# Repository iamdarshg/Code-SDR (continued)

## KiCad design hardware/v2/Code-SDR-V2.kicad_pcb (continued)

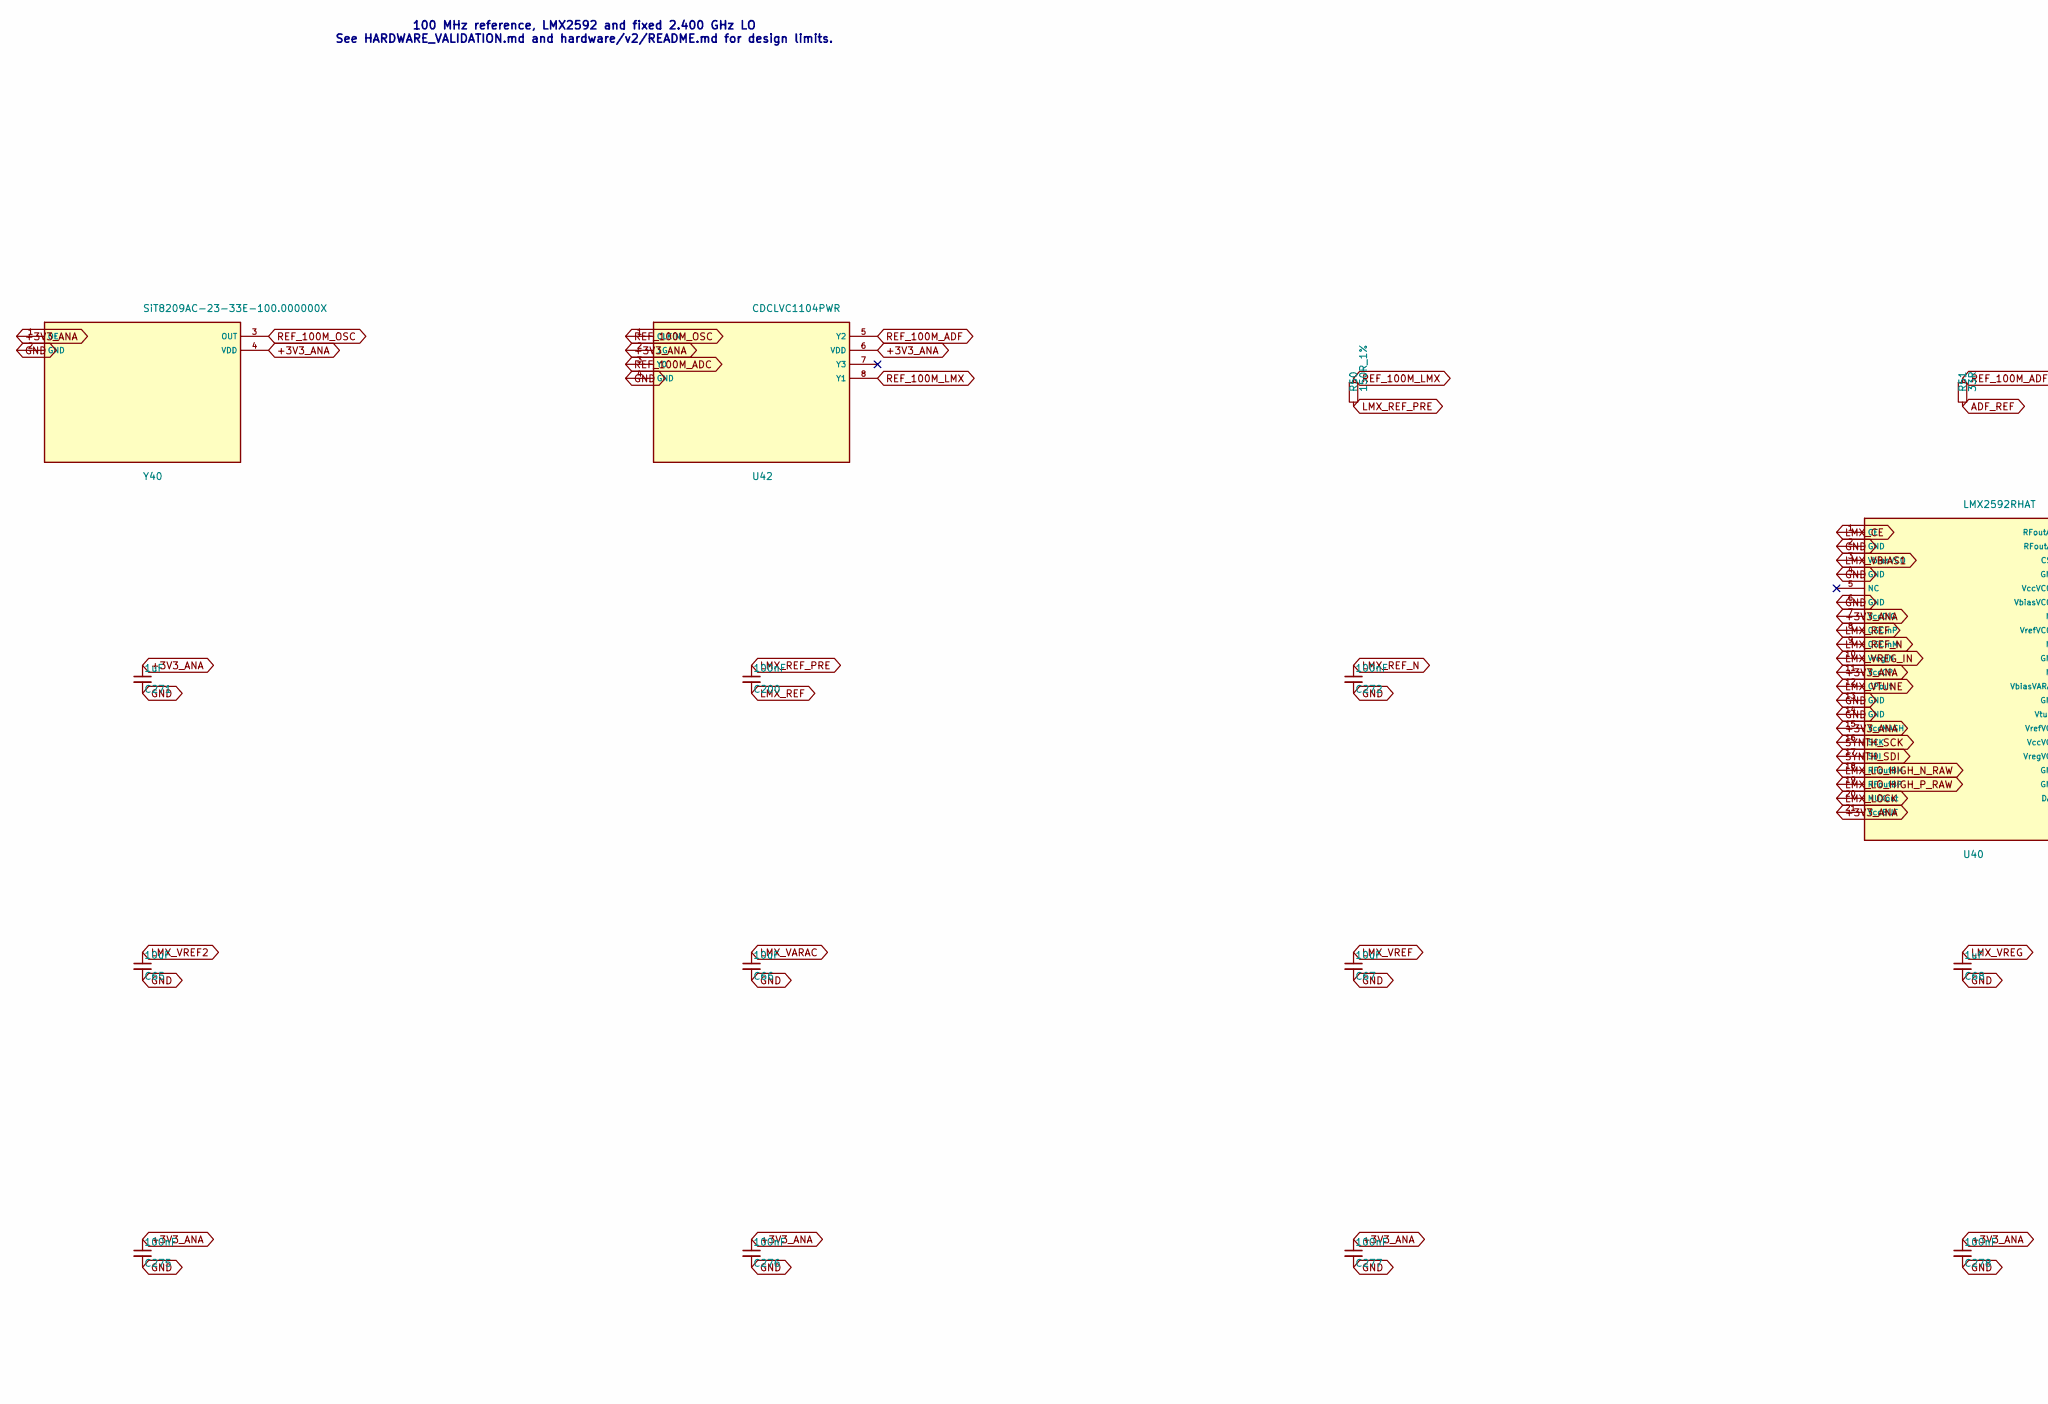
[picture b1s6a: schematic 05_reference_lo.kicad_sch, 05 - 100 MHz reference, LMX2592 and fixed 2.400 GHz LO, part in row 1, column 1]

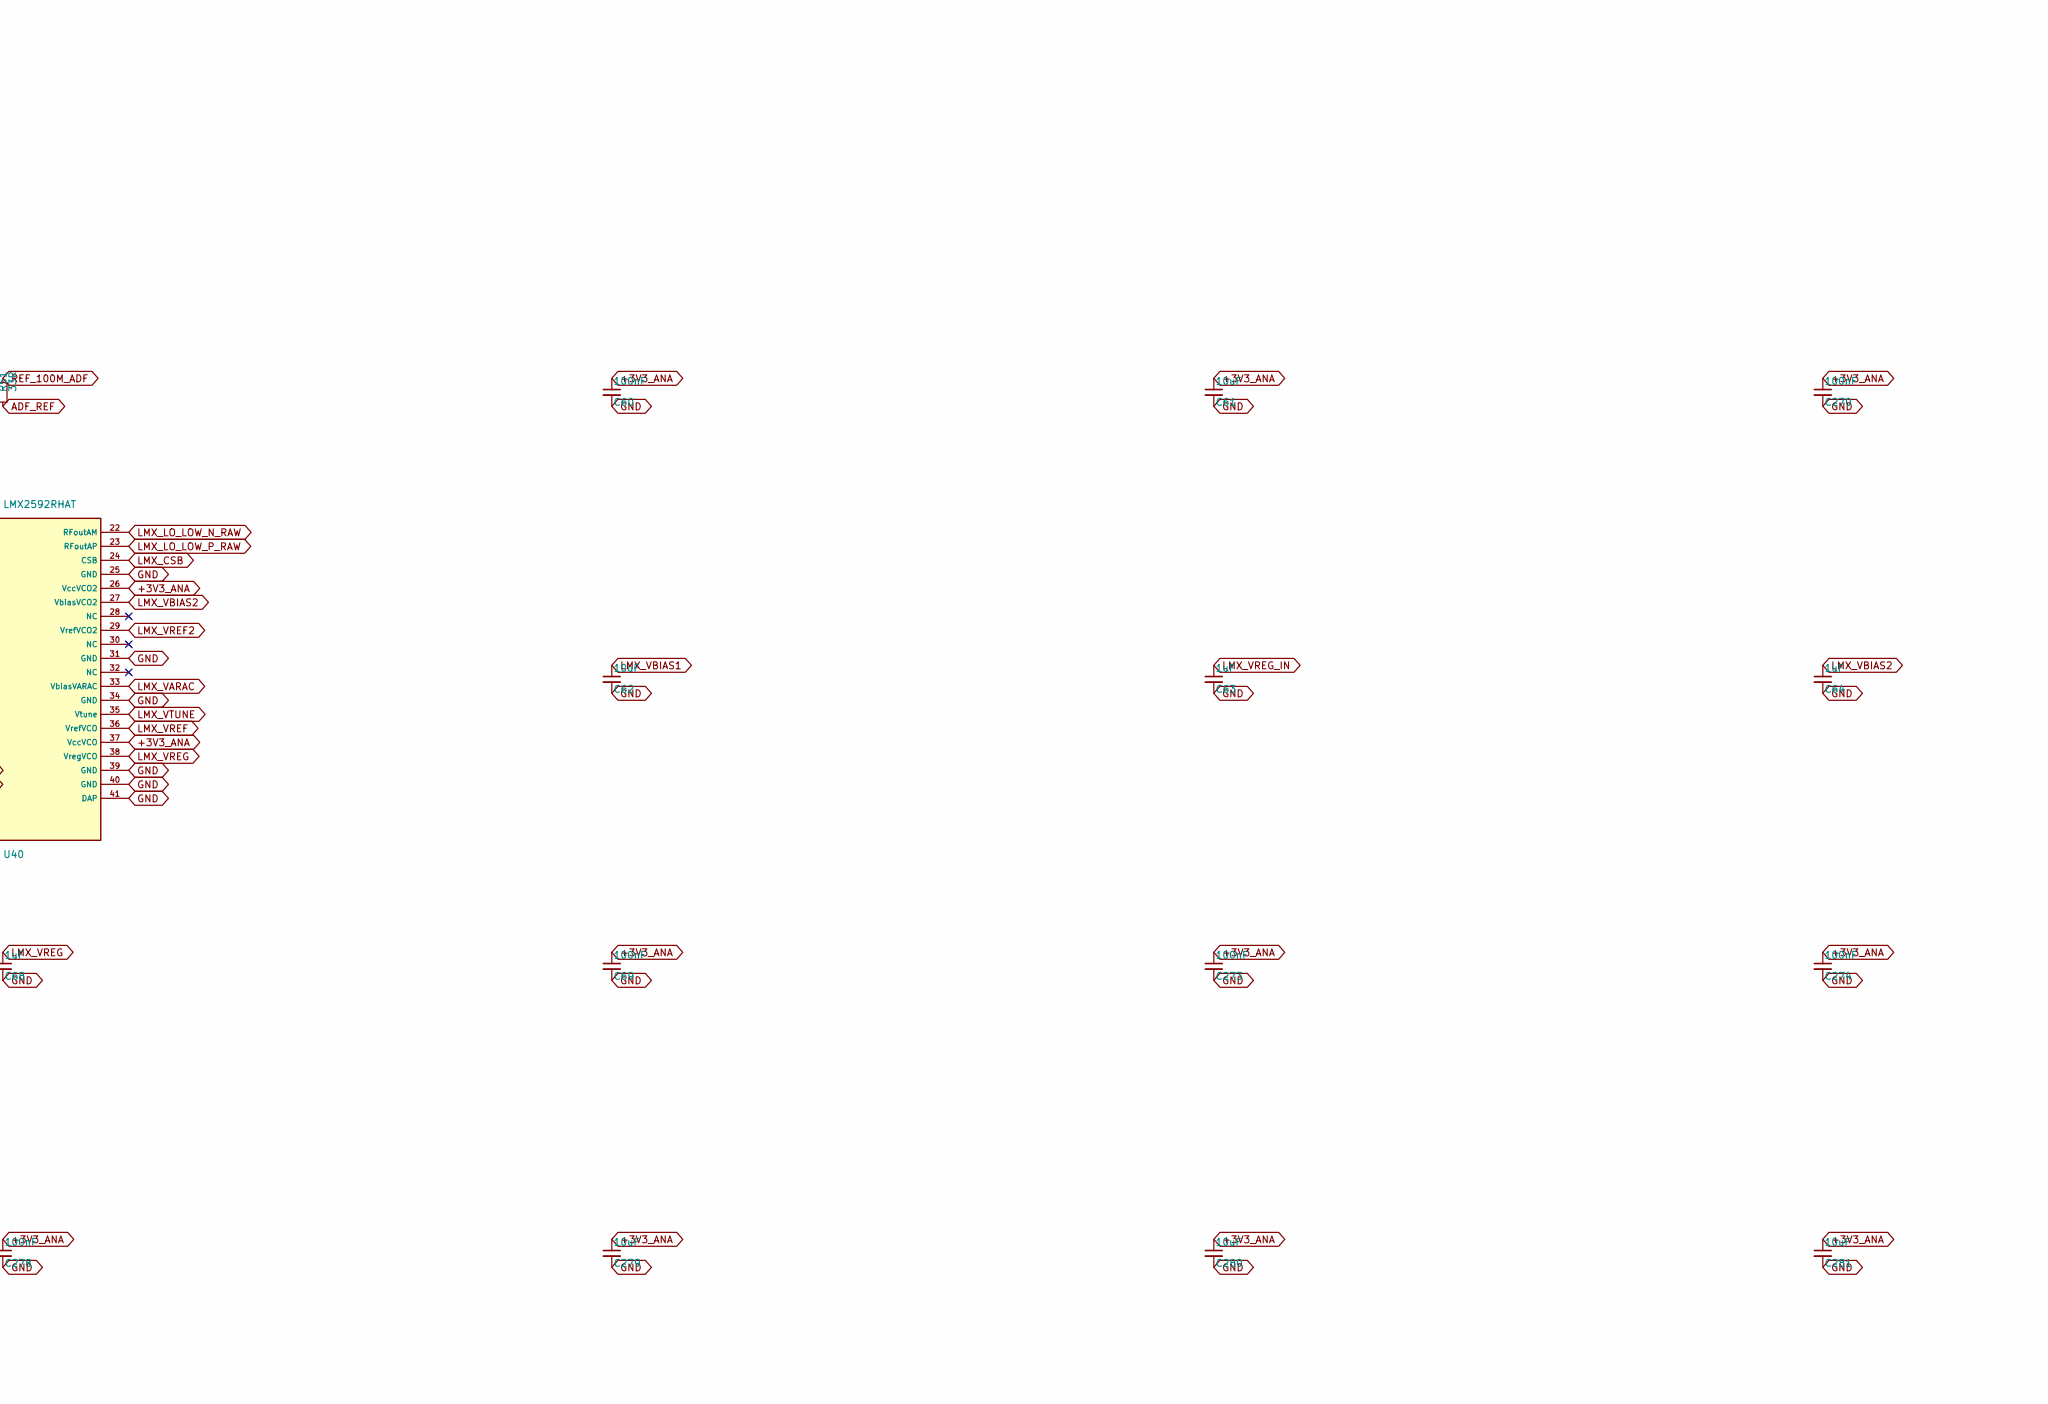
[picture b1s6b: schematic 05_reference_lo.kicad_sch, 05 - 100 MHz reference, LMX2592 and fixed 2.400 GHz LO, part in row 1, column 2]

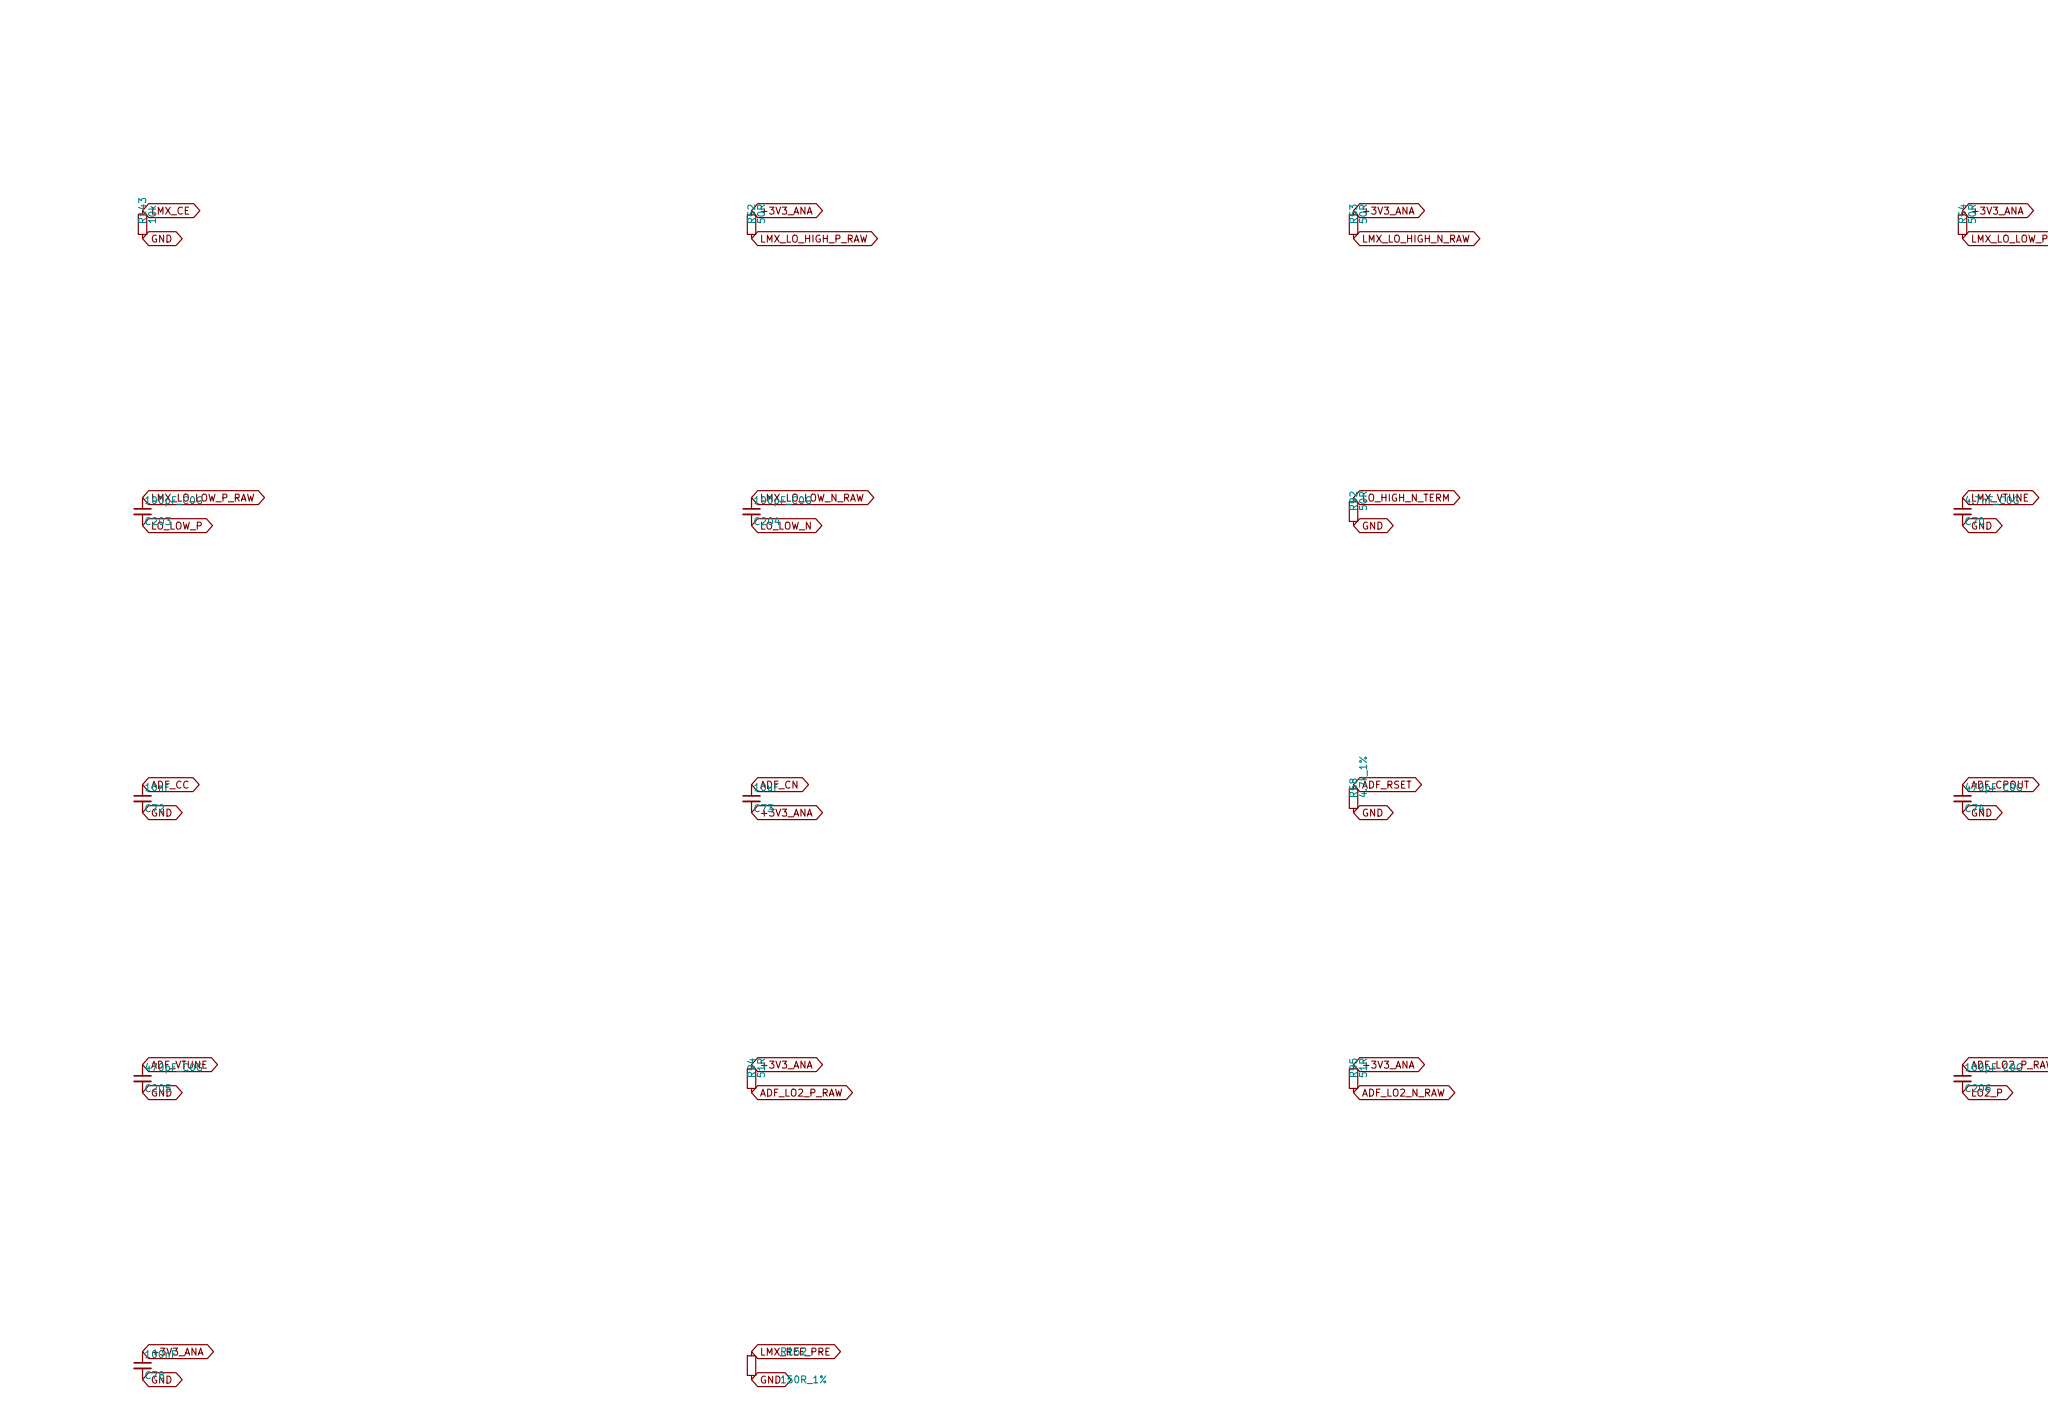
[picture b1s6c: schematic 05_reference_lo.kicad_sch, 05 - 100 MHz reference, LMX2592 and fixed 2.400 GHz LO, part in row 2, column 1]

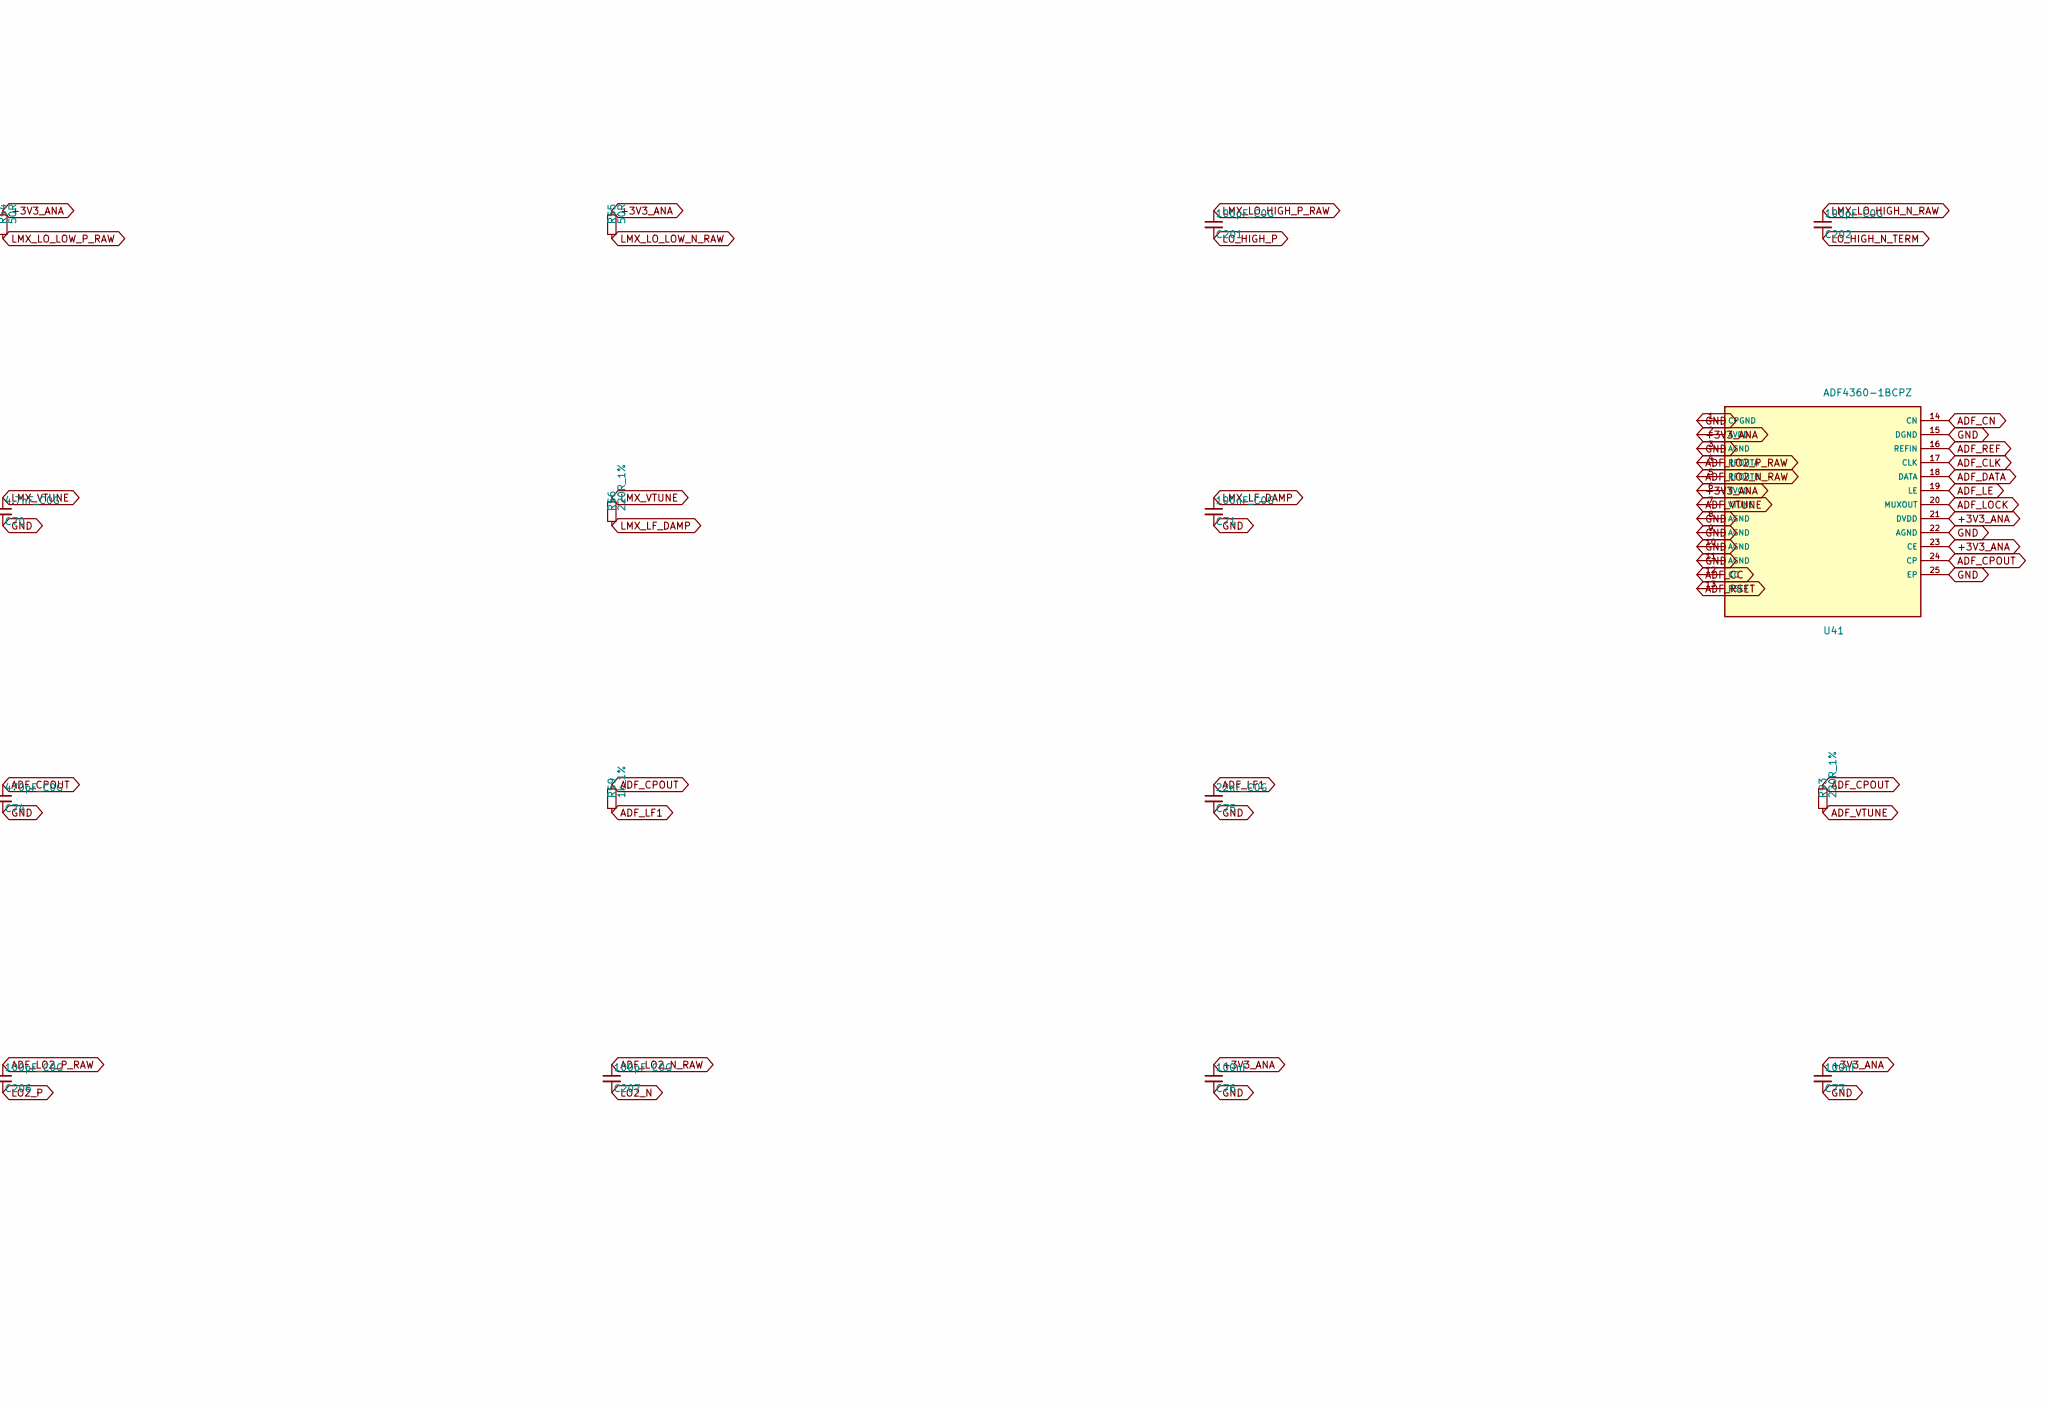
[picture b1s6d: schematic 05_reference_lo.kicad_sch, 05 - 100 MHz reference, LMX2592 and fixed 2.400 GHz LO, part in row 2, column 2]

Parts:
C60, C69, C76, C77, C78, C200, C270, C272, C273, C274, C275, C276, C277, C278: 100nF; C_0402_1005Metric
C61, C62, C65, C66, C67, C73, C279, C280, C281: 10uF; C_0805_2012Metric
C63, C64, C68, C271: 1uF; C_0603_1608Metric
C70: 4.7nF_C0G; C_0402_1005Metric
C71: 100nF_C0G; C_1206_3216Metric
C72: 10nF; C_0402_1005Metric
C74, C205: 470pF_C0G; C_0402_1005Metric
C75: 22nF_C0G; C_0805_2012Metric
C201, C202, C203, C204, C206, C207: 100pF_C0G; C_0201_0603Metric
R50, R152: 150R_1%; R_0402_1005Metric
R51: 33R; R_0402_1005Metric
R52, R53, R54, R55: 50R; R_0402_1005Metric
R56, R93: 220R_1%; R_0402_1005Metric
R58: 4.7k_1%; R_0402_1005Metric
R59: 1k_1%; R_0402_1005Metric
R92: 50R; R_0201_0603Metric
R94, R95: 51R; R_0402_1005Metric
R143: 10k; R_0402_1005Metric
U40: LMX2592RHAT; Texas_RHA0040B_VQFN-40-1EP_6x6mm_P0.5mm_EP4.15x4.15mm_Therm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
U41: ADF4360-1BCPZ; LFCSP-24-1EP_4x4mm_P0.5mm_EP2.5x2.5mm_ThermalVias
U42: CDCLVC1104PWR; TSSOP-8_4.4x3mm_P0.65mm
Y40: SiT8209AC-23-33E-100.000000X; Oscillator_SMD_SiT_PQFN-4Pin_3.2x2.5mm

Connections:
+3V3_ANA: C60.1, C61.1, C69.1, C73.2, C76.1, C77.1, C78.1, C270.1, C271.1, C273.1, C274.1, C275.1, C276.1, C277.1, C278.1, C279.1, C280.1, C281.1, R52.1, R53.1, R54.1, R55.1, R94.1, R95.1, U40.7 (VccDIG), U40.11 (VccCP), U40.15 (VccMASH), U40.21 (VccBUF), U40.26 (VccVCO2), U40.37 (VccVCO), U41.2 (AVDD), U41.6 (VVCO), U41.21 (DVDD), U41.23 (CE), U42.2 (1G), U42.6 (VDD), Y40.1 (OE), Y40.4 (VDD); also elsewhere on the board
ADF_CC: C72.1, U41.12 (CC)
ADF_CLK: U41.17 (CLK); also elsewhere on the board
ADF_CN: C73.1, U41.14 (CN)
ADF_CPOUT: C74.1, R59.1, R93.1, U41.24 (CP)
ADF_DATA: U41.18 (DATA); also elsewhere on the board
ADF_LE: U41.19 (LE); also elsewhere on the board
ADF_LF1: C75.1, R59.2
ADF_LO2_N_RAW: C207.1, R95.2, U41.5 (RFOUTB)
ADF_LO2_P_RAW: C206.1, R94.2, U41.4 (RFOUTA)
ADF_LOCK: U41.20 (MUXOUT); also elsewhere on the board
ADF_REF: R51.2, U41.16 (REFIN)
ADF_RSET: R58.1, U41.13 (RSET)
ADF_VTUNE: C205.1, R93.2, U41.7 (VTUNE)
LMX_CE: R143.1, U40.1 (CE); also elsewhere on the board
LMX_CSB: U40.24 (CSB); also elsewhere on the board
LMX_LF_DAMP: C71.1, R56.2
LMX_LOCK: U40.20 (MUXout); also elsewhere on the board
LMX_LO_HIGH_N_RAW: C202.1, R53.2, U40.18 (RFoutBM)
LMX_LO_HIGH_P_RAW: C201.1, R52.2, U40.19 (RFoutBP)
LMX_LO_LOW_N_RAW: C204.1, R55.2, U40.22 (RFoutAM)
LMX_LO_LOW_P_RAW: C203.1, R54.2, U40.23 (RFoutAP)
LMX_REF: C200.2, U40.8 (OSCinP)
LMX_REF_N: C272.1, U40.9 (OSCinM)
LMX_REF_PRE: C200.1, R50.2, R152.1
LMX_VARAC: C66.1, U40.33 (VbiasVARAC)
LMX_VBIAS1: C62.1, U40.3 (VbiasVCO)
LMX_VBIAS2: C64.1, U40.27 (VbiasVCO2)
LMX_VREF: C67.1, U40.36 (VrefVCO)
LMX_VREF2: C65.1, U40.29 (VrefVCO2)
LMX_VREG: C68.1, U40.38 (VregVCO)
LMX_VREG_IN: C63.1, U40.10 (VregIN)
LMX_VTUNE: C70.1, R56.1, U40.12 (CPout), U40.35 (Vtune)
LO2_N: C207.2; also elsewhere on the board
LO2_P: C206.2; also elsewhere on the board
LO_HIGH_N_TERM: C202.2, R92.1
LO_HIGH_P: C201.2; also elsewhere on the board
LO_LOW_N: C204.2; also elsewhere on the board
LO_LOW_P: C203.2; also elsewhere on the board
REF_100M_ADC: U42.3 (Y0); also elsewhere on the board
REF_100M_ADF: R51.1, U42.5 (Y2)
REF_100M_LMX: R50.1, U42.8 (Y1)
REF_100M_OSC: U42.1 (CLKIN), Y40.3 (OUT)
SYNTH_SCK: U40.16 (SCK); also elsewhere on the board
SYNTH_SDI: U40.17 (SDI); also elsewhere on the board

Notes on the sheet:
100 MHz reference, LMX2592 and fixed 2.400 GHz LO See HARDWARE_VALIDATION.md and hardware/v2/README.md for design limits.

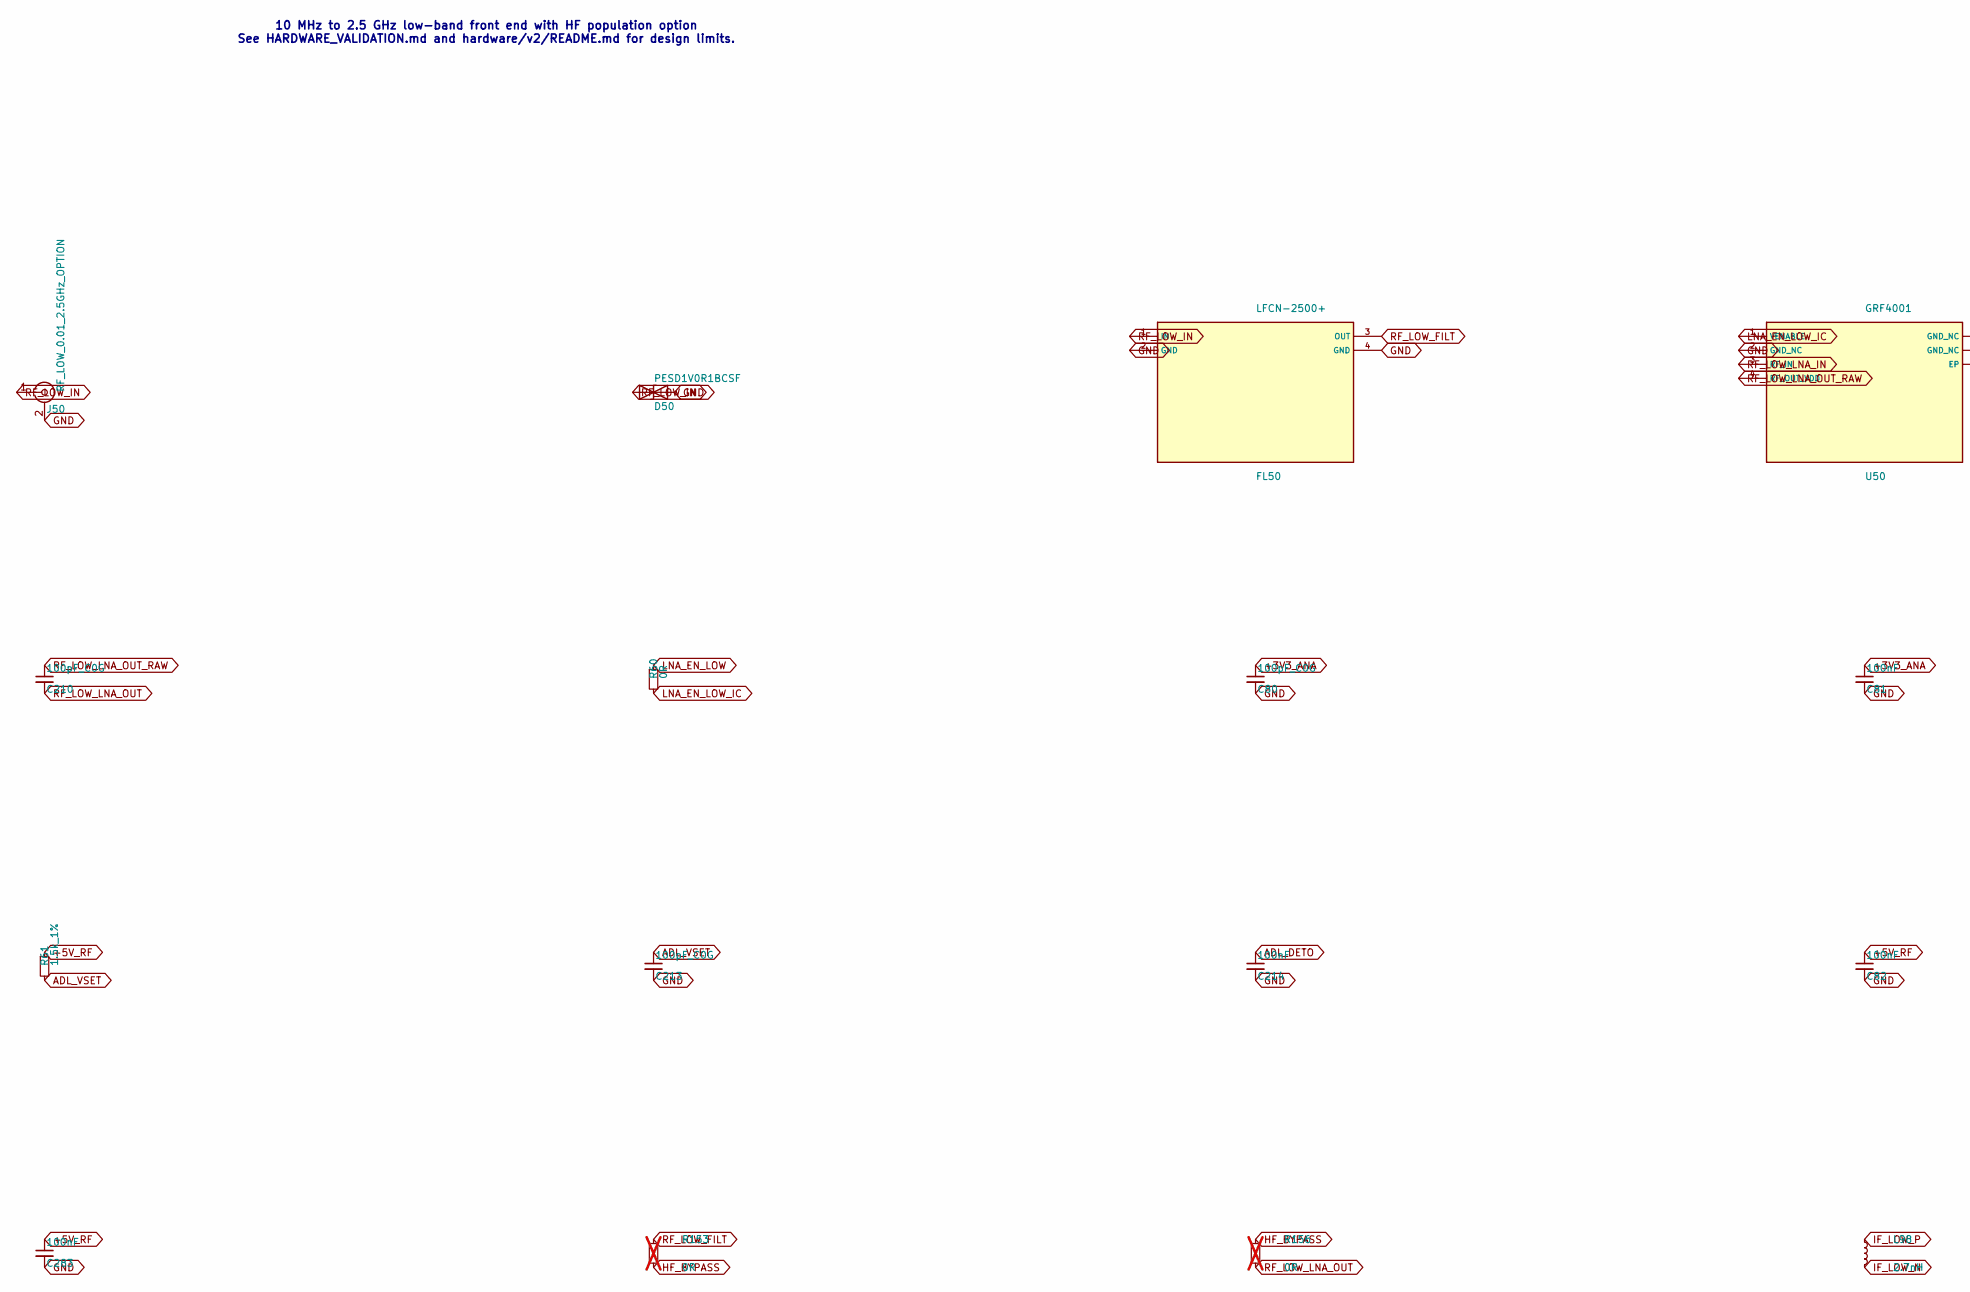
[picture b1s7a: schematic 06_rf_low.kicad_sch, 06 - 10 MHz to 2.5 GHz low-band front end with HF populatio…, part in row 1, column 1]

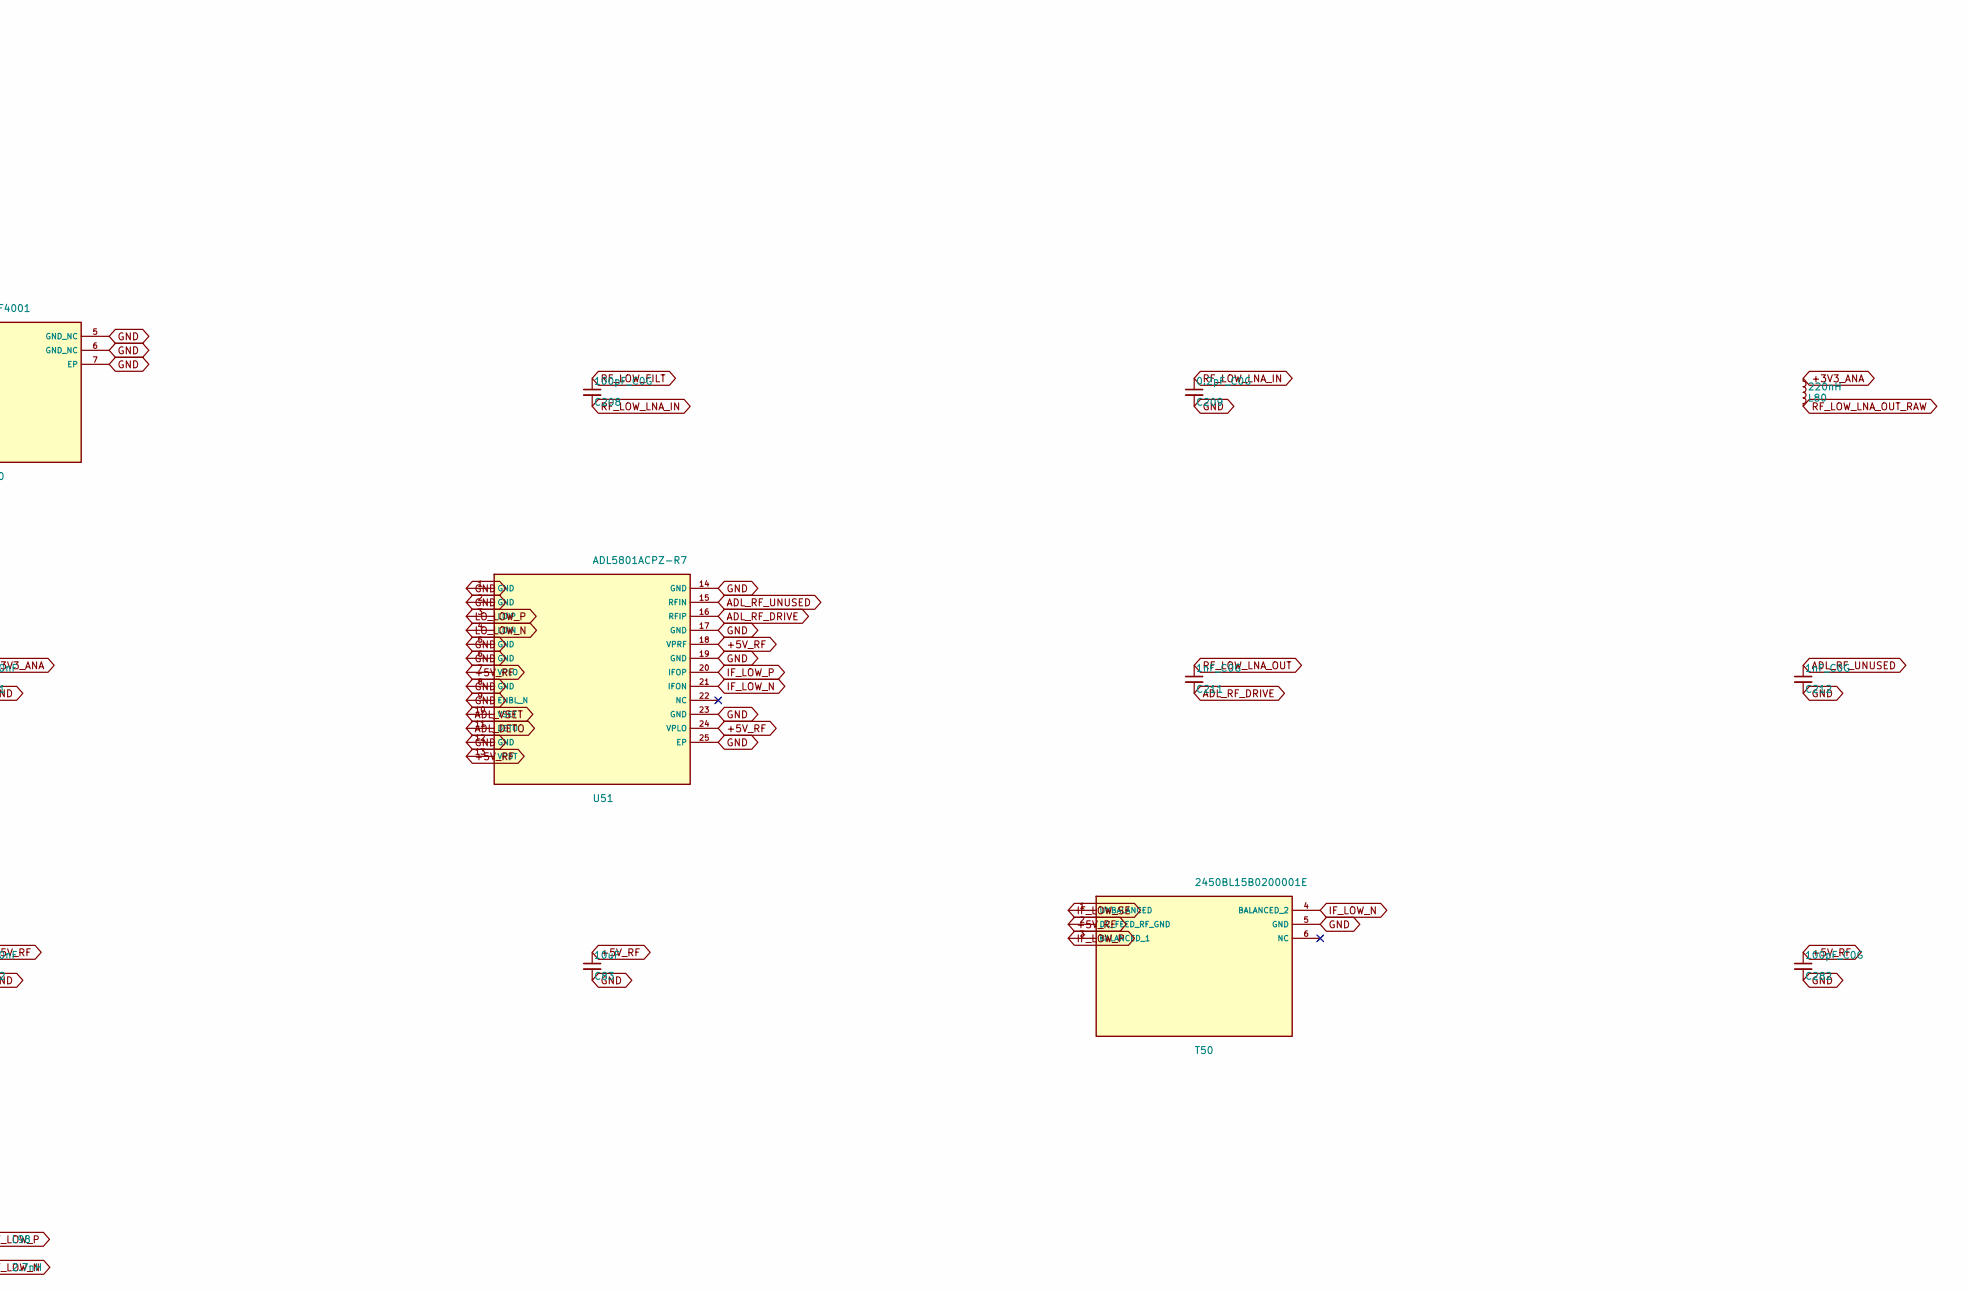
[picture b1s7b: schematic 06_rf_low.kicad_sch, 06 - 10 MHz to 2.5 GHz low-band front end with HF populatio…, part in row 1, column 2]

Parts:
C80, C213, C282: 100pF_C0G; C_0402_1005Metric
C81, C82, C214, C283: 100nF; C_0402_1005Metric
C83: 10uF; C_0805_2012Metric
C208, C210: 100pF_C0G; C_0201_0603Metric
C209: 0.2pF_C0G; C_0201_0603Metric
C211, C212: 1nF_C0G; C_0402_1005Metric
D50: PESD1V0R1BCSF; SOD962-2_DSN0603
FL50: LFCN-2500+; MiniCircuits_FV1206
J50: RF_LOW_0.01_2.5GHz_OPTION; SMA_Molex_73251-1153_EdgeMount_Horizontal
L80: 220nH; L_0603_1608Metric_Pad1.05x0.95mm_HandSolder
L98: 2.7nH; L_0402_1005Metric
R60: 0R; R_0402_1005Metric
R61: 1.5k_1%; R_0402_1005Metric
R153, R156: 0R; R_0402_1005Metric; not fitted
T50: 2450BL15B0200001E; Johanson_0805_6P_Balun
U50: GRF4001; GRF_DFN6_1.5x1.5mm
U51: ADL5801ACPZ-R7; LFCSP-24-1EP_4x4mm_P0.5mm_EP2.5x2.5mm_ThermalVias

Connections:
+3V3_ANA: C80.1, C81.1, L80.1; also elsewhere on the board
+5V_RF: C82.1, C83.1, C282.1, C283.1, R61.1, T50.2 (DC_FEED_RF_GND), U51.7 (VPLO), U51.13 (VPDT), U51.18 (VPRF), U51.24 (VPLO); also elsewhere on the board
ADL_DETO: C214.1, U51.11 (DETO)
ADL_RF_DRIVE: C211.2, U51.16 (RFIP)
ADL_RF_UNUSED: C212.1, U51.15 (RFIN)
ADL_VSET: C213.1, R61.2, U51.10 (VSET)
HF_BYPASS: R153.2, R156.1
IF_LOW_N: L98.2, T50.4 (BALANCED_2), U51.21 (IFON)
IF_LOW_P: L98.1, T50.3 (BALANCED_1), U51.20 (IFOP)
IF_LOW_SE: T50.1 (UNBALANCED); also elsewhere on the board
LNA_EN_LOW: R60.1; also elsewhere on the board
LNA_EN_LOW_IC: R60.2, U50.1 (VENABLE)
LO_LOW_N: U51.4 (LOIN); also elsewhere on the board
LO_LOW_P: U51.3 (LOIP); also elsewhere on the board
RF_LOW_FILT: C208.1, FL50.3 (OUT), R153.1
RF_LOW_IN: D50.1 (A1), FL50.1 (IN), J50.1 (In)
RF_LOW_LNA_IN: C208.2, C209.1, U50.3 (RF_IN)
RF_LOW_LNA_OUT: C210.2, C211.1, R156.2
RF_LOW_LNA_OUT_RAW: C210.1, L80.2, U50.4 (RF_OUT_VDD)

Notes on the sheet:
10 MHz to 2.5 GHz low-band front end with HF population option See HARDWARE_VALIDATION.md and hardware/v2/README.md for design limits.
